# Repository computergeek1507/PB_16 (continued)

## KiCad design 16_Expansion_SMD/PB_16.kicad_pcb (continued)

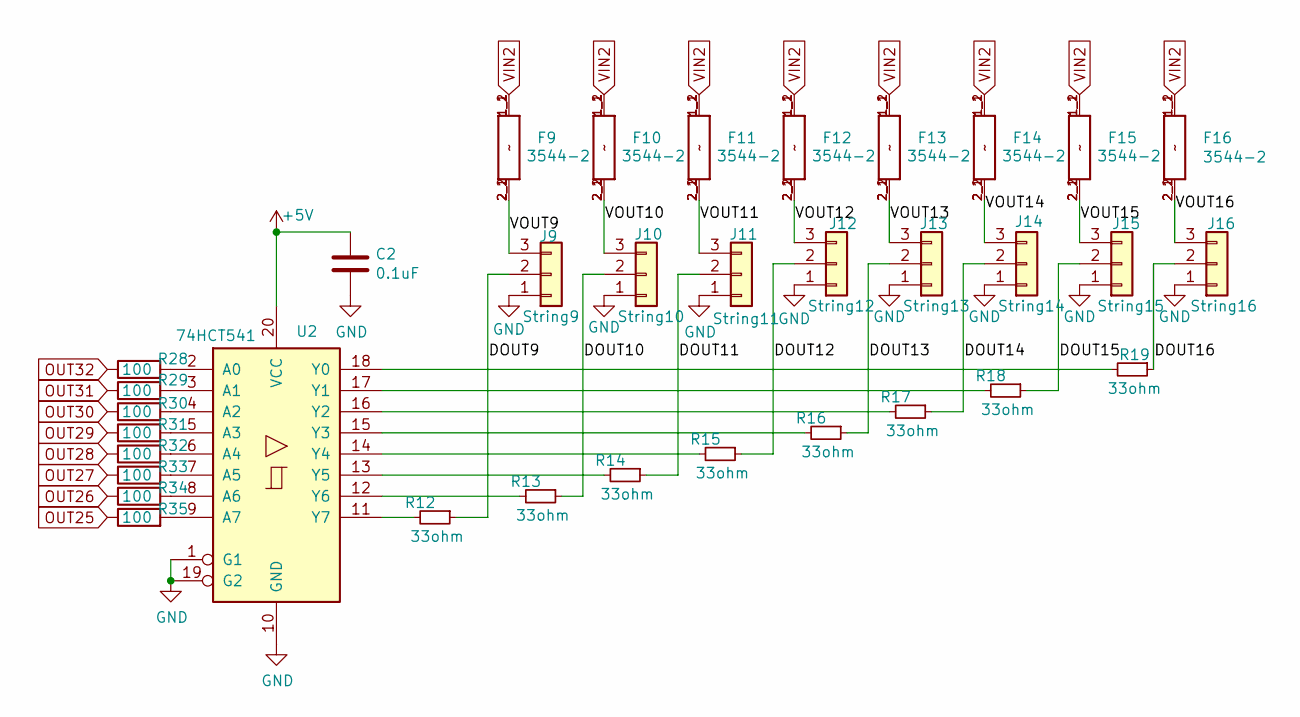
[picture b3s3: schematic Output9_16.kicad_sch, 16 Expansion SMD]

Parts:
C2: 0.1uF; C_0402_1005Metric; MPN 08055C104KAT2A; Digi-Key_PN 478-1395-1-ND
F9, F10, F11, F12, F13, F14, F15, F16: 3544-2; FUSE_3544-2; MPN 3544-2; Digi-Key_PN 36-3544-2-ND
J9: String9; PhoenixContact_MCV_3.81mm_3.5mm_1x03_Vertical; MPN 1843619/OSTTJ0311530; Digi-Key_PN 277-5737-ND/ED10555-ND
J10: String10; PhoenixContact_MCV_3.81mm_3.5mm_1x03_Vertical; MPN 1843619/OSTTJ0311530; Digi-Key_PN 277-5737-ND/ED10555-ND
J11: String11; PhoenixContact_MCV_3.81mm_3.5mm_1x03_Vertical; MPN 1843619/OSTTJ0311530; Digi-Key_PN 277-5737-ND/ED10555-ND
J12: String12; PhoenixContact_MCV_3.81mm_3.5mm_1x03_Vertical; MPN 1843619/OSTTJ0311530; Digi-Key_PN 277-5737-ND/ED10555-ND
J13: String13; PhoenixContact_MCV_3.81mm_3.5mm_1x03_Vertical; MPN 1843619/OSTTJ0311530; Digi-Key_PN 277-5737-ND/ED10555-ND
J14: String14; PhoenixContact_MCV_3.81mm_3.5mm_1x03_Vertical; MPN 1843619/OSTTJ0311530; Digi-Key_PN 277-5737-ND/ED10555-ND
J15: String15; PhoenixContact_MCV_3.81mm_3.5mm_1x03_Vertical; MPN 1843619/OSTTJ0311530; Digi-Key_PN 277-5737-ND/ED10555-ND
J16: String16; PhoenixContact_MCV_3.81mm_3.5mm_1x03_Vertical; MPN 1843619/OSTTJ0311530; Digi-Key_PN 277-5737-ND/ED10555-ND
R12, R13, R14, R15, R16, R17, R18, R19: 33ohm; R_0603_1608Metric; MPN RC0603JR-0733RL; LCSC_PN C23140
R28, R29, R30, R31, R32, R33, R34, R35: 100; R_0603_1608Metric
U2: 74HCT541; TSSOP-20_4.4x6.5mm_P0.65mm; LCSC C131314

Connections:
+5V: C2.1, U2.20 (VCC); also elsewhere on the board
/Output 9-16/DOUT9: J9.2, R12.1
/Output 9-16/DOUT10: J10.2, R13.1
/Output 9-16/DOUT11: J11.2, R14.1
/Output 9-16/DOUT12: J12.2, R15.1
/Output 9-16/DOUT13: J13.2, R16.1
/Output 9-16/DOUT14: J14.2, R17.1
/Output 9-16/DOUT15: J15.2, R18.1
/Output 9-16/DOUT16: J16.2, R19.1
/Output 9-16/VOUT9: F9.2_1 (2), F9.2_2 (2), J9.3
/Output 9-16/VOUT10: F10.2_1 (2), F10.2_2 (2), J10.3
/Output 9-16/VOUT11: F11.2_1 (2), F11.2_2 (2), J11.3
/Output 9-16/VOUT12: F12.2_1 (2), F12.2_2 (2), J12.3
/Output 9-16/VOUT13: F13.2_1 (2), F13.2_2 (2), J13.3
/Output 9-16/VOUT14: F14.2_1 (2), F14.2_2 (2), J14.3
/Output 9-16/VOUT15: F15.2_1 (2), F15.2_2 (2), J15.3
/Output 9-16/VOUT16: F16.2_1 (2), F16.2_2 (2), J16.3
GND: C2.2, J9.1, J10.1, J11.1, J12.1, J13.1, J14.1, J15.1, J16.1, U2.1 (G1), U2.10 (GND), U2.19 (G2); also elsewhere on the board
unnamed: R28.2, U2.2 (A0)
unnamed: R29.2, U2.3 (A1)
unnamed: R30.2, U2.4 (A2)
unnamed: R31.2, U2.5 (A3)
unnamed: R32.2, U2.6 (A4)
unnamed: R33.2, U2.7 (A5)
unnamed: R34.2, U2.8 (A6)
unnamed: R35.2, U2.9 (A7)
unnamed: R19.2, U2.18 (Y0)
unnamed: R18.2, U2.17 (Y1)
unnamed: R17.2, U2.16 (Y2)
unnamed: R16.2, U2.15 (Y3)
unnamed: R15.2, U2.14 (Y4)
unnamed: R14.2, U2.13 (Y5)
unnamed: R13.2, U2.12 (Y6)
unnamed: R12.2, U2.11 (Y7)
OUT25: R35.1; also elsewhere on the board
OUT26: R34.1; also elsewhere on the board
OUT27: R33.1; also elsewhere on the board
OUT28: R32.1; also elsewhere on the board
OUT29: R31.1; also elsewhere on the board
OUT30: R30.1; also elsewhere on the board
OUT31: R29.1; also elsewhere on the board
OUT32: R28.1; also elsewhere on the board
VIN2: F9.1_1 (1), F9.1_2 (1), F10.1_1 (1), F10.1_2 (1), F11.1_1 (1), F11.1_2 (1), F12.1_1 (1), F12.1_2 (1), F13.1_1 (1), F13.1_2 (1), F14.1_1 (1), F14.1_2 (1), F15.1_1 (1), F15.1_2 (1), F16.1_1 (1), F16.1_2 (1); also elsewhere on the board

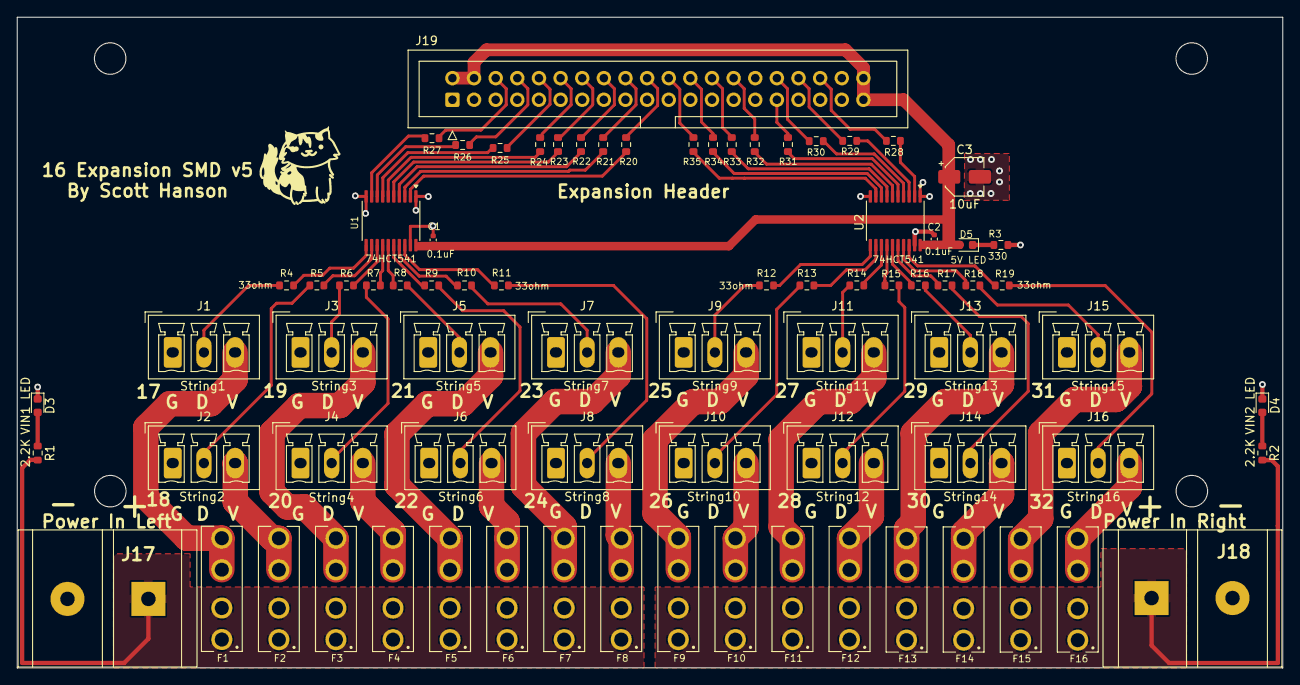
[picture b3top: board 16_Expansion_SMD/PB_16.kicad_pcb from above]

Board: 2 copper layers, 148.6 x 76.4 mm, 82 parts (0 on the bottom side), 87 nets.

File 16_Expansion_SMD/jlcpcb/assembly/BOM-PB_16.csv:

Comment,Designator,Footprint,LCSC
1K,"R1,R2",R_0805_2012Metric_Pad1.15x1.40mm_HandSolder,C17513
330,R3,R_0805_2012Metric_Pad1.15x1.40mm_HandSolder,C17630
VIN1 LED,"D3,D4,D5",LED_0805_2012Metric_Pad1.15x1.40mm_HandSolder,C2297
100,"R20,R21,R22,R23,R24,R25,R26,R27,R28,R29,R30,R31,R32,R33,R34,R35",R_0603_1608Metric_Pad0.98x0.95mm_HandSolder,C25804
0.1uF,"C1,C2",C_0805_2012Metric_Pad1.15x1.40mm_HandSolder,C49678
74HC245,"U1,U2",SOIC-20W_7.5x12.8mm_P1.27mm,C5625
10uF,C3,CP_Elec_4x5.3,C72485
String2,J2,"PhoenixContact_MCV_1,5_3-G-3.5_1x03_P3.50mm_Vertical",
String5,J5,"PhoenixContact_MCV_1,5_3-G-3.5_1x03_P3.50mm_Vertical",
String6,J6,"PhoenixContact_MCV_1,5_3-G-3.5_1x03_P3.50mm_Vertical",
String7,J7,"PhoenixContact_MCV_1,5_3-G-3.5_1x03_P3.50mm_Vertical",
String8,J8,"PhoenixContact_MCV_1,5_3-G-3.5_1x03_P3.50mm_Vertical",
String9,J9,"PhoenixContact_MCV_1,5_3-G-3.5_1x03_P3.50mm_Vertical",
String10,J10,"PhoenixContact_MCV_1,5_3-G-3.5_1x03_P3.50mm_Vertical",
String11,J11,"PhoenixContact_MCV_1,5_3-G-3.5_1x03_P3.50mm_Vertical",
String12,J12,"PhoenixContact_MCV_1,5_3-G-3.5_1x03_P3.50mm_Vertical",
String13,J13,"PhoenixContact_MCV_1,5_3-G-3.5_1x03_P3.50mm_Vertical",
String14,J14,"PhoenixContact_MCV_1,5_3-G-3.5_1x03_P3.50mm_Vertical",
String15,J15,"PhoenixContact_MCV_1,5_3-G-3.5_1x03_P3.50mm_Vertical",
String16,J16,"PhoenixContact_MCV_1,5_3-G-3.5_1x03_P3.50mm_Vertical",
3544-2,F1,FUSE_3544-2,
3544-2,F7,FUSE_3544-2,
3544-2,F14,FUSE_3544-2,
3544-2,F2,FUSE_3544-2,
3544-2,F6,FUSE_3544-2,
3544-2,F8,FUSE_3544-2,
3544-2,F9,FUSE_3544-2,
3544-2,F10,FUSE_3544-2,
3544-2,F16,FUSE_3544-2,
3544-2,F5,FUSE_3544-2,
3544-2,F3,FUSE_3544-2,
3544-2,F13,FUSE_3544-2,
33,RN1,R_Array_SIP8,
3544-2,F11,FUSE_3544-2,
33,RN3,R_Array_SIP8,
33,RN4,R_Array_SIP8,
33,RN2,R_Array_SIP8,
3544-2,F4,FUSE_3544-2,
String1,J1,"PhoenixContact_MCV_1,5_3-G-3.5_1x03_P3.50mm_Vertical",
String3,J3,"PhoenixContact_MCV_1,5_3-G-3.5_1x03_P3.50mm_Vertical",
String4,J4,"PhoenixContact_MCV_1,5_3-G-3.5_1x03_P3.50mm_Vertical",
3544-2,F15,FUSE_3544-2,
3544-2,F12,FUSE_3544-2,
Expansion Header,J19,IDC-Header_2x20_P2.54mm_Vertical,
Power In Left,J17,BARRIER_BLOCK_1ROW_2POS_P9.5MM,
Power In Right,J18,BARRIER_BLOCK_1ROW_2POS_P9.5MM,

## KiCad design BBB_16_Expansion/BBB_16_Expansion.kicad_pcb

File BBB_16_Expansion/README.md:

# Copyright and Disclaimer
Copyright: Scott Hanson

This documentation describes Open Hardware and is licensed under the CERN Open Hardware License Version 2 - Strongly Reciprocal. (CERN-OHL-S)

You may redistribute and modify this documentation under the terms of the CERN OHL-S-v2 (https://ohwr.org/cern_ohl_s_v2.txt). This documentation is distributed WITHOUT ANY EXPRESS OR IMPLIED WARRANTY, INCLUDING OF MERCHANTABILITY, SATISFACTORY QUALITY AND FITNESS FOR A PARTICULAR PURPOSE. Please see the CERN OHL v2-S for applicable conditions

**Under CERN OHL-S-v2, derivative work must be publicly released as defined in subsection 3.3**

# BBB 16 Expansion

**This board is untested, use at your own risk**

The BBB16 Expansion is a version of the BBB16 for the Falcon v4 Expansion Boards. It can be used with three expansion boards, 48 outputs. The design is surface mount. All the design files are open source and available on github.

To order PCBs upload the "GERBER-BBB_16_Expansion.zip" file in the "jlcpcb\gerber" folder to jlcpcb.com. Enable the SMD service, 'BOM-BBB_16_Expansion.csv' is the SMD BOM and 'POS-BBB_16_Expansion.csv' is the SMD CPL position file.

## [Part BOM](https://github.com/computergeek1507/PB_16/raw/master/BBB_16_Expansion/BBB_16_Expansion_BOM.ods)

## [Interactive BOM](https://computergeek1507.github.io/PB_16/BBB_16_Expansion/bom/ibom)

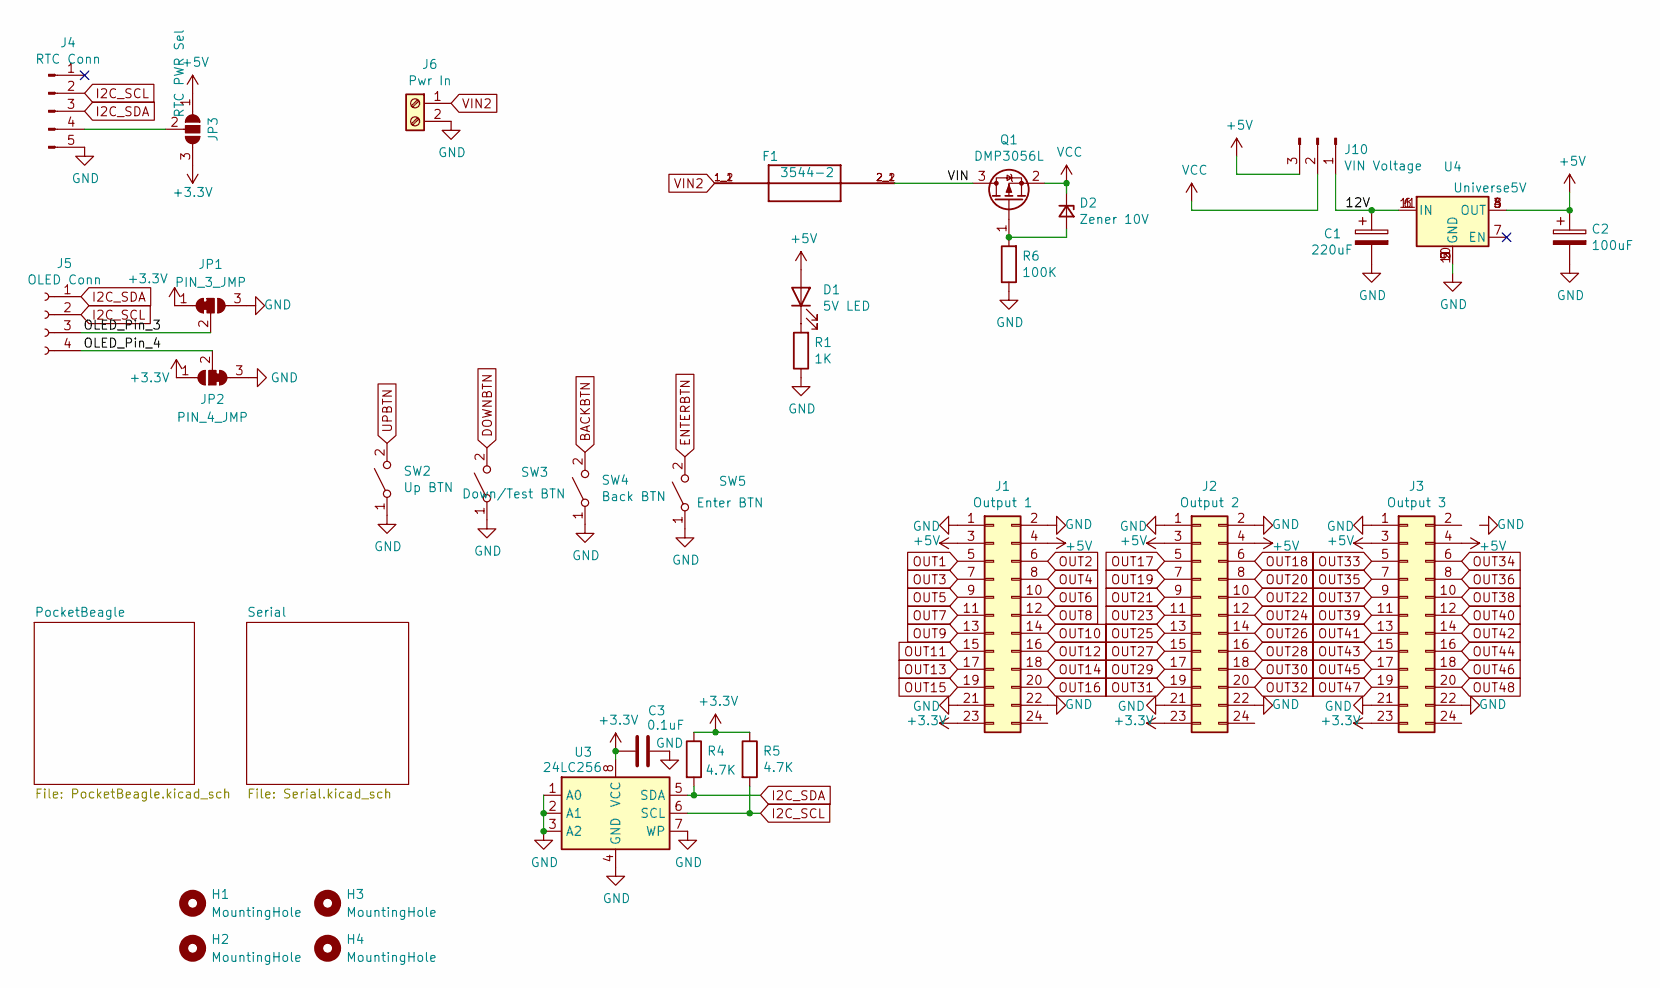
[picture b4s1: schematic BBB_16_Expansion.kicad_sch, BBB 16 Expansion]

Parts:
C1: 220uF; CP_Radial_D10.0mm_P5.00mm; MPN ECA-1HM221; Digi-Key_PN P5183-ND
C2: 100uF; CP_Elec_6.3x5.4_Nichicon; MPN UWX1C101MCL1GB; Digi-Key_PN 493-2105-1-ND
C3: 0.1uF; C_0603_1608Metric_Pad1.08x0.95mm_HandSolder; MPN CC0603KRX7R9BB104; Digi-Key_PN 1276-1007-1-ND
D1: 5V LED; LED_0603_1608Metric_Pad1.05x0.95mm_HandSolder; MPN LTST-C171GKT; Digi-Key_PN 160-1423-1-ND
D2: Zener 10V; D_SOD-123; MPN MMSZ5240B-7-F; Digi-Key_PN MMSZ5240B-FDICT-ND
F1: 3544-2; FUSE_3544-2; MPN 3544-2; Digi-Key_PN 36-3544-2-ND
H1, H2, H3, H4: MountingHole; MountingHole_3.5mm
J1: Output 1; OST_302-S241; MPN Z-S311024S1GK1A; Digi-Key_PN ED10525-ND
J2: Output 2; OST_302-S241; MPN Z-S311024S1GK1A; Digi-Key_PN ED10525-ND
J3: Output 3; OST_302-S241; MPN Z-S311024S1GK1A; Digi-Key_PN ED10525-ND
J4: RTC Conn; PinHeader_1x05_P2.54mm_Vertical; MPN MTP125-1105S1; Digi-Key_PN 732-5318-ND
J5: OLED Conn; OLED-SSD1306-128X64-I2C-THT; MPN A2541HWV-4P; Digi-Key_PN S7002-ND
J6: Pwr In; PHOENIX_MKDS1_2-3.81; MPN 1727010; Digi-Key_PN 277-1947-ND
J10: VIN Voltage; PinHeader_1x03_P2.54mm_Vertical; MPN 61300311121; Digi-Key_PN 732-5316-ND
JP1: PIN_3_JMP; SolderJumper-3_P1mm_Bridged12
JP2: PIN_4_JMP; SolderJumper-3_P1mm_Bridged23
JP3: RTC PWR Sel; SolderJumper-3_P1.3mm_Open_Pad1.0x1.5mm
Q1: DMP3056L; SOT-23; MPN DMP3056L-7; Digi-Key_PN DMP3056L-7DICT-ND
R1: 1K; R_0603_1608Metric_Pad0.98x0.95mm_HandSolder; MPN RC0805FR-071KL; Digi-Key_PN 311-1.00KCRCT-ND
R4, R5: 4.7K; R_0603_1608Metric_Pad0.98x0.95mm_HandSolder; MPN RC0805JR-074K7L; Digi-Key_PN 311-4.7KARCT-ND
R6: 100K; R_0603_1608Metric_Pad0.98x0.95mm_HandSolder; MPN RT0603BRD07100KL; Digi-Key_PN YAG1235CT-ND
SW2: Up BTN; SW_PUSH_6mm; MPN 1825910-6; Digi-Key_PN 450-1650-ND
SW3: Down/Test BTN; SW_PUSH_6mm; MPN 1825910-6; Digi-Key_PN 450-1650-ND
SW4: Back BTN; SW_PUSH_6mm; MPN 1825910-6; Digi-Key_PN 450-1650-ND
SW5: Enter BTN; SW_PUSH_6mm; MPN 1825910-6; Digi-Key_PN 450-1650-ND
U3: 24LC256; SOIC-8_3.9x4.9mm_P1.27mm; MPN 24LC256T-I/SN; Digi-Key_PN 24LC256T-I/SNCT-ND
U4: Universe5V; Universal_5V_Horizontal; MPN OKI-78SR-5/1.5-W36-C; Digi-Key_PN 811-2196-5-ND

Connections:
+3V3: C3.2, J1.23, J2.23, J3.23, JP1.1 (A), JP2.1 (A), JP3.3 (B), R4.1, R5.1, U3.8 (VCC); also elsewhere on the board
+5V: C2.1, D1.2 (A), J1.3, J1.4, J2.3, J2.4, J3.3, J3.4, J10.3, JP3.1 (A), U4.3 (OUT), U4.4 (OUT), U4.8 (OUT); also elsewhere on the board
/12V: C1.1, J10.1, U4.1 (IN), U4.6 (IN), U4.11 (IN)
/OLED_Pin_3: J5.3, JP1.2 (C)
/OLED_Pin_4: J5.4, JP2.2 (C)
/VIN: F1.2_1 (2), F1.2_2 (2), Q1.3 (D)
BACKBTN: SW4.2 (B); also elsewhere on the board
DOWNBTN: SW3.2 (B); also elsewhere on the board
ENTERBTN: SW5.2 (B); also elsewhere on the board
GND: C1.2, C2.2, C3.1, J1.1, J1.2, J1.21, J1.22, J2.1, J2.2, J2.21, J2.22, J3.1, J3.21, J3.22, J4.5, J6.2, JP1.3 (B), JP2.3 (B), R1.1, R6.1, SW2.1 (A), SW3.1 (A), SW4.1 (A), SW5.1 (A), U3.1 (A0), U3.2 (A1), U3.3 (A2), U3.4 (GND), U3.7 (WP), U4.2 (GND), U4.5 (GND), U4.9 (GND), U4.10 (GND); also elsewhere on the board
I2C_SCL: J4.2, J5.2, R5.2, U3.6 (SCL); also elsewhere on the board
I2C_SDA: J4.3, J5.1, R4.2, U3.5 (SDA); also elsewhere on the board
unnamed: D1.1 (K), R1.2
unnamed: D2.2 (A), Q1.1 (G), R6.2
unnamed: J4.4, JP3.2 (C)
OUT1: J1.5; also elsewhere on the board
OUT2: J1.6; also elsewhere on the board
OUT3: J1.7; also elsewhere on the board
OUT4: J1.8; also elsewhere on the board
OUT5: J1.9; also elsewhere on the board
OUT6: J1.10; also elsewhere on the board
OUT7: J1.11; also elsewhere on the board
OUT8: J1.12; also elsewhere on the board
OUT9: J1.13; also elsewhere on the board
OUT10: J1.14; also elsewhere on the board
OUT11: J1.15; also elsewhere on the board
OUT12: J1.16; also elsewhere on the board
OUT13: J1.17; also elsewhere on the board
OUT14: J1.18; also elsewhere on the board
OUT15: J1.19; also elsewhere on the board
OUT16: J1.20; also elsewhere on the board
OUT17: J2.5; also elsewhere on the board
OUT18: J2.6; also elsewhere on the board
OUT19: J2.7; also elsewhere on the board
OUT20: J2.8; also elsewhere on the board
OUT21: J2.9; also elsewhere on the board
OUT22: J2.10; also elsewhere on the board
OUT23: J2.11; also elsewhere on the board
OUT24: J2.12; also elsewhere on the board
OUT25: J2.13; also elsewhere on the board
OUT26: J2.14; also elsewhere on the board
OUT27: J2.15; also elsewhere on the board
OUT28: J2.16; also elsewhere on the board
OUT29: J2.17; also elsewhere on the board
OUT30: J2.18; also elsewhere on the board
OUT31: J2.19; also elsewhere on the board
OUT32: J2.20; also elsewhere on the board
OUT33: J3.5; also elsewhere on the board
OUT34: J3.6; also elsewhere on the board
OUT35: J3.7; also elsewhere on the board
OUT36: J3.8; also elsewhere on the board
OUT37: J3.9; also elsewhere on the board
OUT38: J3.10; also elsewhere on the board
OUT39: J3.11; also elsewhere on the board
OUT40: J3.12; also elsewhere on the board
OUT41: J3.13; also elsewhere on the board
OUT42: J3.14; also elsewhere on the board
OUT43: J3.15; also elsewhere on the board
OUT44: J3.16; also elsewhere on the board
OUT45: J3.17; also elsewhere on the board
OUT46: J3.18; also elsewhere on the board
OUT47: J3.19; also elsewhere on the board
OUT48: J3.20; also elsewhere on the board
UPBTN: SW2.2 (B); also elsewhere on the board
VCC: D2.1 (K), J10.2, Q1.2 (S)
VIN2: F1.1_1 (1), F1.1_2 (1), J6.1

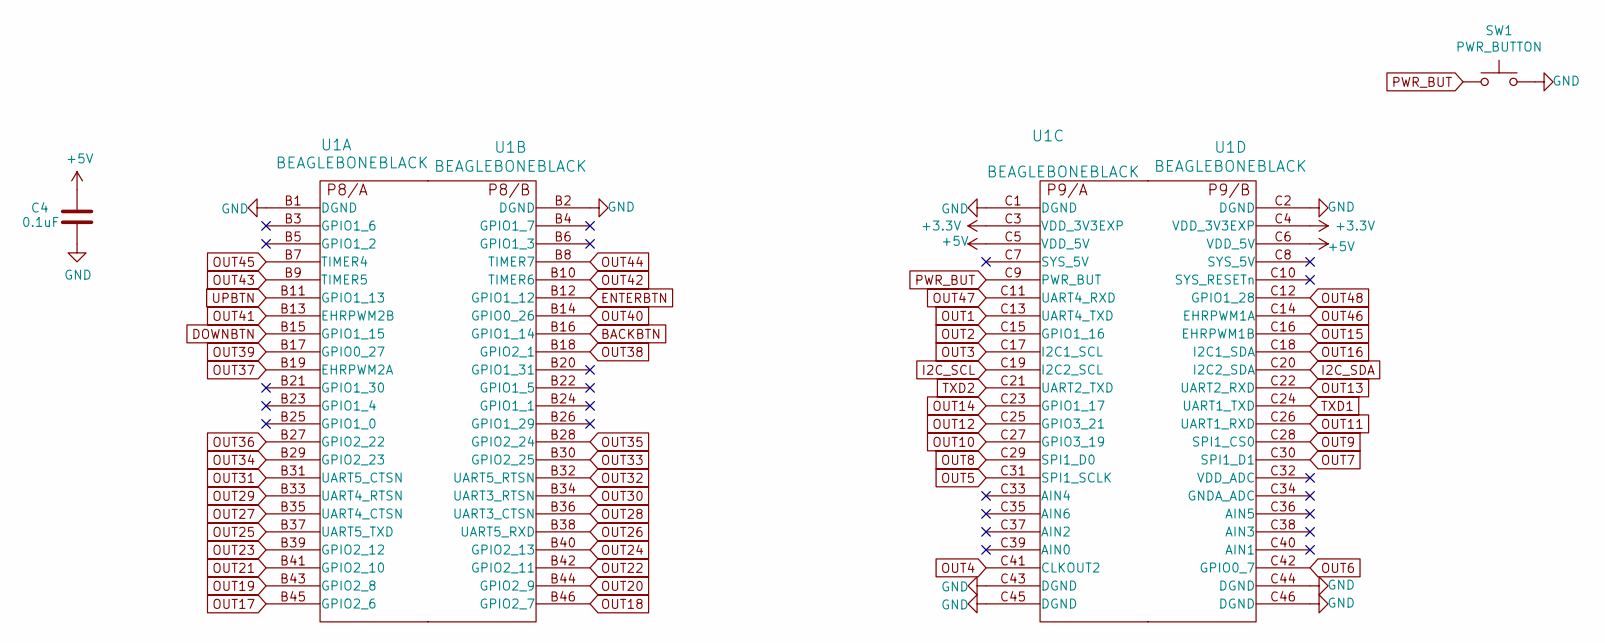
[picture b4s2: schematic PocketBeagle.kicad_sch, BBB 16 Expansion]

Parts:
C4: 0.1uF; C_0603_1608Metric_Pad1.08x0.95mm_HandSolder; MPN CC0603KRX7R9BB104; Digi-Key_PN 1276-1007-1-ND
SW1: PWR_BUTTON; SW_PUSH_6mm; MPN 1825910-6; Digi-Key_PN 450-1650-ND
U1: BEAGLEBONEBLACK

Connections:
+3V3: U1.C3 (VDD_3V3EXP), U1.C4 (VDD_3V3EXP); also elsewhere on the board
+5V: C4.1, U1.C5 (VDD_5V), U1.C6 (VDD_5V); also elsewhere on the board
BACKBTN: U1.B16 (GPIO1_14); also elsewhere on the board
DOWNBTN: U1.B15 (GPIO1_15); also elsewhere on the board
ENTERBTN: U1.B12 (GPIO1_12); also elsewhere on the board
GND: C4.2, SW1.2, U1.B1 (DGND), U1.B2 (DGND), U1.C1 (DGND), U1.C2 (DGND), U1.C43 (DGND), U1.C44 (DGND), U1.C45 (DGND), U1.C46 (DGND); also elsewhere on the board
I2C_SCL: U1.C19 (I2C2_SCL); also elsewhere on the board
I2C_SDA: U1.C20 (I2C2_SDA); also elsewhere on the board
OUT1: U1.C13 (UART4_TXD); also elsewhere on the board
OUT2: U1.C15 (GPIO1_16); also elsewhere on the board
OUT3: U1.C17 (I2C1_SCL); also elsewhere on the board
OUT4: U1.C41 (CLKOUT2); also elsewhere on the board
OUT5: U1.C31 (SPI1_SCLK); also elsewhere on the board
OUT6: U1.C42 (GPIO0_7); also elsewhere on the board
OUT7: U1.C30 (SPI1_D1); also elsewhere on the board
OUT8: U1.C29 (SPI1_D0); also elsewhere on the board
OUT9: U1.C28 (SPI1_CS0); also elsewhere on the board
OUT10: U1.C27 (GPIO3_19); also elsewhere on the board
OUT11: U1.C26 (UART1_RXD); also elsewhere on the board
OUT12: U1.C25 (GPIO3_21); also elsewhere on the board
OUT13: U1.C22 (UART2_RXD); also elsewhere on the board
OUT14: U1.C23 (GPIO1_17); also elsewhere on the board
OUT15: U1.C16 (EHRPWM1B); also elsewhere on the board
OUT16: U1.C18 (I2C1_SDA); also elsewhere on the board
OUT17: U1.B45 (GPIO2_6); also elsewhere on the board
OUT18: U1.B46 (GPIO2_7); also elsewhere on the board
OUT19: U1.B43 (GPIO2_8); also elsewhere on the board
OUT20: U1.B44 (GPIO2_9); also elsewhere on the board
OUT21: U1.B41 (GPIO2_10); also elsewhere on the board
OUT22: U1.B42 (GPIO2_11); also elsewhere on the board
OUT23: U1.B39 (GPIO2_12); also elsewhere on the board
OUT24: U1.B40 (GPIO2_13); also elsewhere on the board
OUT25: U1.B37 (UART5_TXD); also elsewhere on the board
OUT26: U1.B38 (UART5_RXD); also elsewhere on the board
OUT27: U1.B35 (UART4_CTSN); also elsewhere on the board
OUT28: U1.B36 (UART3_CTSN); also elsewhere on the board
OUT29: U1.B33 (UART4_RTSN); also elsewhere on the board
OUT30: U1.B34 (UART3_RTSN); also elsewhere on the board
OUT31: U1.B31 (UART5_CTSN); also elsewhere on the board
OUT32: U1.B32 (UART5_RTSN); also elsewhere on the board
OUT33: U1.B30 (GPIO2_25); also elsewhere on the board
OUT34: U1.B29 (GPIO2_23); also elsewhere on the board
OUT35: U1.B28 (GPIO2_24); also elsewhere on the board
OUT36: U1.B27 (GPIO2_22); also elsewhere on the board
OUT37: U1.B19 (EHRPWM2A); also elsewhere on the board
OUT38: U1.B18 (GPIO2_1); also elsewhere on the board
OUT39: U1.B17 (GPIO0_27); also elsewhere on the board
OUT40: U1.B14 (GPIO0_26); also elsewhere on the board
OUT41: U1.B13 (EHRPWM2B); also elsewhere on the board
OUT42: U1.B10 (TIMER6); also elsewhere on the board
OUT43: U1.B9 (TIMER5); also elsewhere on the board
OUT44: U1.B8 (TIMER7); also elsewhere on the board
OUT45: U1.B7 (TIMER4); also elsewhere on the board
OUT46: U1.C14 (EHRPWM1A); also elsewhere on the board
OUT47: U1.C11 (UART4_RXD); also elsewhere on the board
OUT48: U1.C12 (GPIO1_28); also elsewhere on the board
PWR_BUT: SW1.1, U1.C9 (PWR_BUT)
TXD1: U1.C24 (UART1_TXD); also elsewhere on the board
TXD2: U1.C21 (UART2_TXD); also elsewhere on the board
UPBTN: U1.B11 (GPIO1_13); also elsewhere on the board

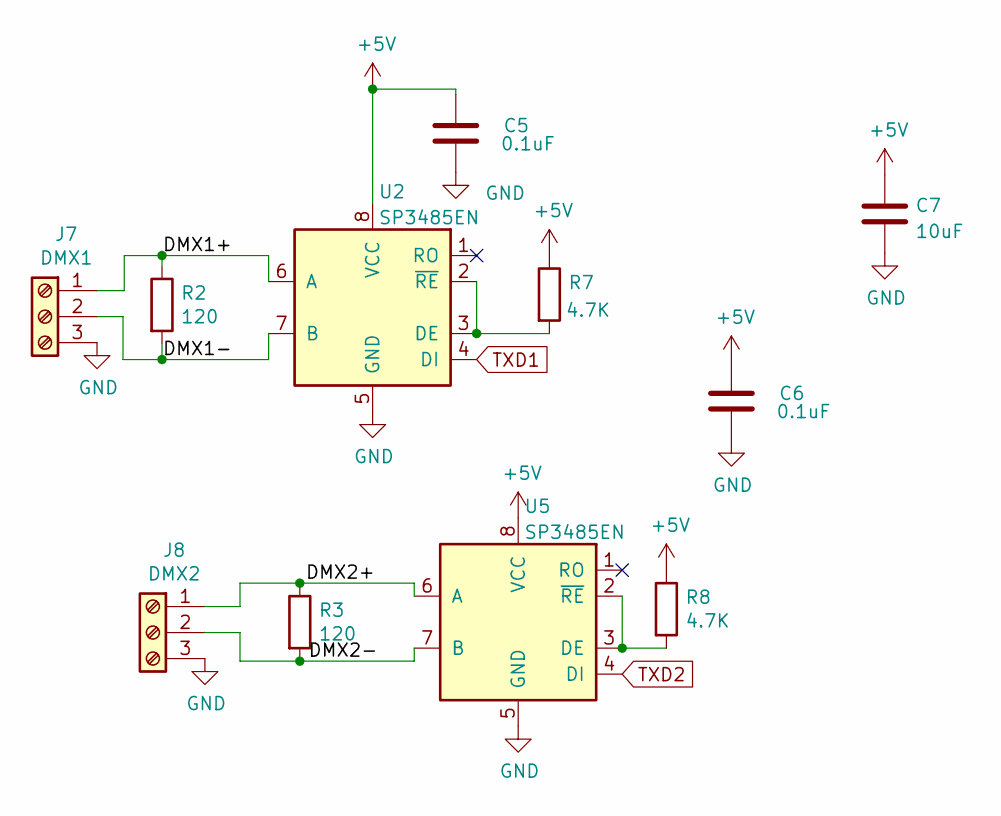
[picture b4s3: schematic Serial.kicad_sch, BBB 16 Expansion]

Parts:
C5, C6: 0.1uF; C_0603_1608Metric_Pad1.08x0.95mm_HandSolder; MPN CC0603KRX7R9BB104; Digi-Key_PN 1276-1007-1-ND
C7: 10uF; CP_Elec_4x5.3; MPN UWT1C100MCL1GB; Digi-Key_PN 493-2173-1-ND
J7: DMX1; PhoenixContact_MCV_1,5_3-G-3.81_1x03_P3.81mm_Vertical; MPN EBWA-03-B; Digi-Key_PN 2057-EBWA-03-B-ND
J8: DMX2; PhoenixContact_MCV_1,5_3-G-3.81_1x03_P3.81mm_Vertical; MPN EBWA-03-B; Digi-Key_PN 2057-EBWA-03-B-ND
R2, R3: 120; R_0603_1608Metric_Pad0.98x0.95mm_HandSolder; MPN RC0805JR-07120RL; Digi-Key_PN 311-120ARCT-ND
R7, R8: 4.7K; R_0603_1608Metric_Pad0.98x0.95mm_HandSolder; MPN RC0805JR-074K7L; Digi-Key_PN 311-4.7KARCT-ND
U2, U5: SP3485EN; SOIC-8_3.9x4.9mm_P1.27mm; MPN SP485EEN-L; Digi-Key_PN 1016-1171-5-ND

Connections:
+5V: C5.1, C6.1, C7.1, R7.1, R8.1, U2.8 (VCC), U5.8 (VCC); also elsewhere on the board
/Serial/DMX1+: J7.1, R2.1, U2.6 (A)
/Serial/DMX1-: J7.2, R2.2, U2.7 (B)
/Serial/DMX2+: J8.1, R3.1, U5.6 (A)
/Serial/DMX2-: J8.2, R3.2, U5.7 (B)
GND: C5.2, C6.2, C7.2, J7.3, J8.3, U2.5 (GND), U5.5 (GND); also elsewhere on the board
unnamed: R7.2, U2.2 (~RE), U2.3 (DE)
unnamed: R8.2, U5.2 (~RE), U5.3 (DE)
TXD1: U2.4 (DI); also elsewhere on the board
TXD2: U5.4 (DI); also elsewhere on the board

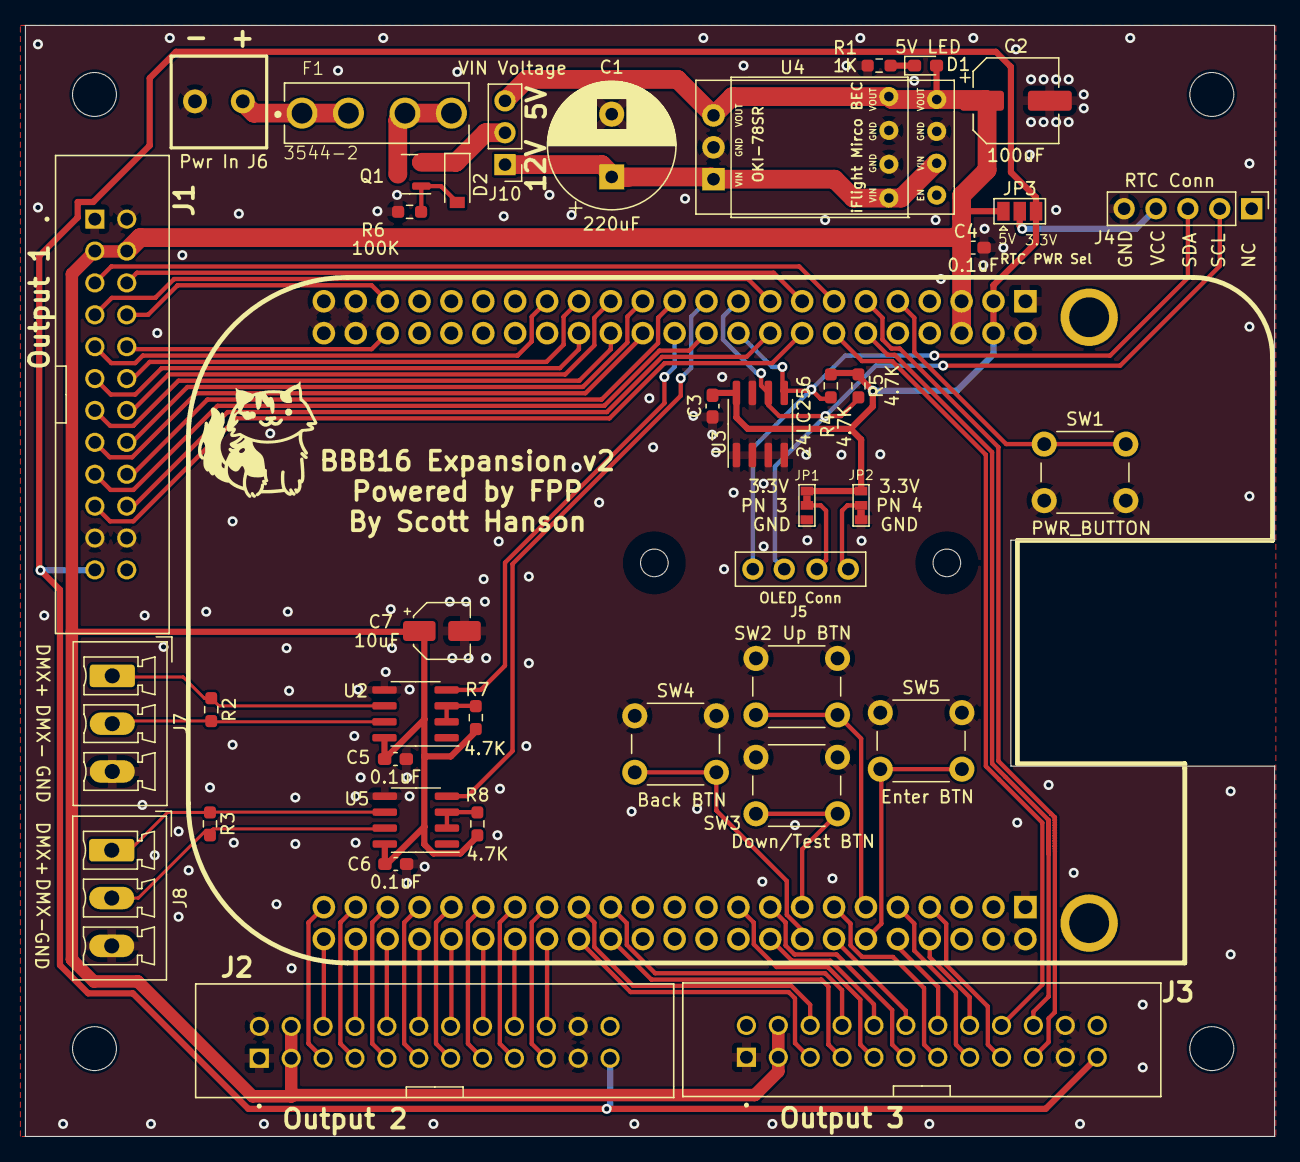
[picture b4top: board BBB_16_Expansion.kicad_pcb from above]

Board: 2 copper layers, 99.5 x 88.5 mm, 45 parts (0 on the bottom side), 75 nets.

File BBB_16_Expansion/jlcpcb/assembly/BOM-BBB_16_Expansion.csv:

Comment,Designator,Footprint,LCSC
100uF,C2,CP_Elec_6.3x5.4_Nichicon,C134723
0.1uF,"C3,C4,C5,C6",C_0603_1608Metric_Pad1.08x0.95mm_HandSolder,C14663
DMP3056L,Q1,SOT-23,C150724
Zener 10V,D2,D_SOD-123,C173431
120,"R2,R3",R_0603_1608Metric_Pad0.98x0.95mm_HandSolder,C17437
1K,R1,R_0603_1608Metric_Pad0.98x0.95mm_HandSolder,C17513
4.7K,"R4,R5,R7,R8",R_0603_1608Metric_Pad0.98x0.95mm_HandSolder,C17673
Output 1,"J1,J2,J3",OST_302-S241,C221083
OLED Conn,J5,OLED-SSD1306-128X64-I2C-THT,C225501
5V LED,D1,LED_0603_1608Metric_Pad1.05x0.95mm_HandSolder,C2297
100K,R6,R_0603_1608Metric_Pad0.98x0.95mm_HandSolder,C25803
RTC Conn,J4,PinHeader_1x05_P2.54mm_Vertical,C358687
DMX1,"J7,J8",PhoenixContact_MCV_3.81mm_3.5mm_1x03_Vertical,C36780
PWR_BUTTON,"SW1,SW2,SW3,SW4,SW5",SW_PUSH_6mm,C428628
VIN Voltage,J10,PinHeader_1x03_P2.54mm_Vertical,C49257
3544-2,F1,FUSE_3544-2,C492610
24LC256,U3,SOIC-8_3.9x4.9mm_P1.27mm,C6482
SP3485EN,"U2,U5",SOIC-8_3.9x4.9mm_P1.27mm,C6855
Pwr In,J6,PHOENIX_MKDS1_2-3.81,C69811
10uF,C7,CP_Elec_4x5.3,C72485
220uF,C1,CP_Radial_D10.0mm_P5.00mm,C88784
Universe5V,U4,Universal_5V_Horizontal,
BEAGLEBONEBLACK,U1,BEAGLEBONEBLACK,

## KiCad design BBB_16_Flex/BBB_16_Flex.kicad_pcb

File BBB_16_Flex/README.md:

# Copyright and Disclaimer
Copyright: Scott Hanson

This documentation describes Open Hardware and is licensed under the CERN Open Hardware License Version 2 - Strongly Reciprocal. (CERN-OHL-S)

You may redistribute and modify this documentation under the terms of the CERN OHL-S-v2 (https://ohwr.org/cern_ohl_s_v2.txt). This documentation is distributed WITHOUT ANY EXPRESS OR IMPLIED WARRANTY, INCLUDING OF MERCHANTABILITY, SATISFACTORY QUALITY AND FITNESS FOR A PARTICULAR PURPOSE. Please see the CERN OHL v2-S for applicable conditions

**Under CERN OHL-S-v2, derivative work must be publicly released as defined in subsection 3.3**

# BBB 16 Flex

The BBB16 Flex is a version of the BBB16 for the HolidayCoro Flex System. It can be used with all three flex boards, 48 outputs. The design is surface mount. All the design files are open source and available on github.

## [Part BOM](https://github.com/computergeek1507/PB_16/raw/master/BBB_16_Flex/BBB_16_Flex_BOM.ods)

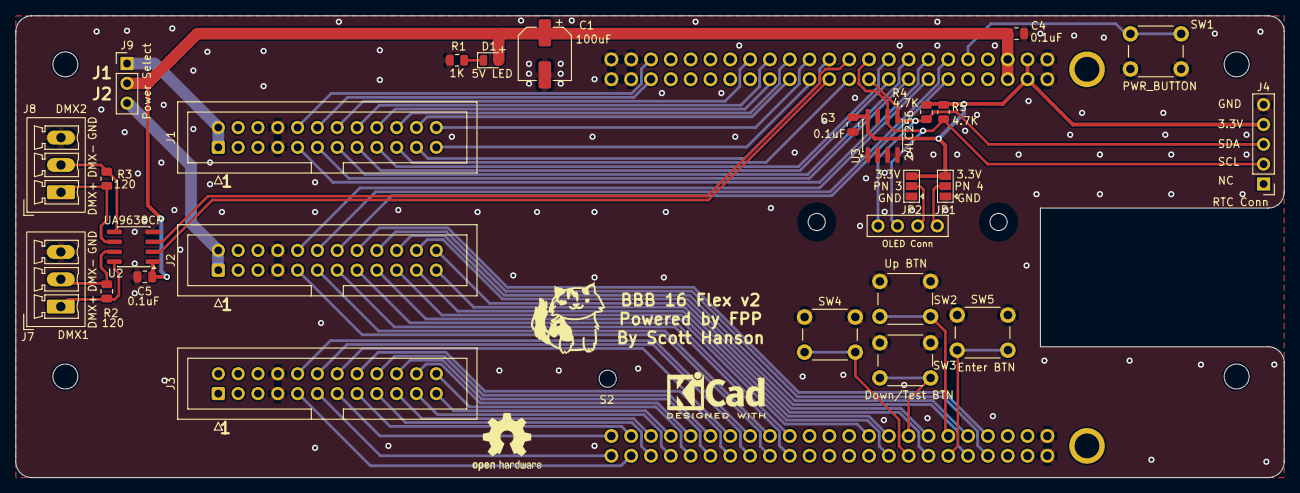
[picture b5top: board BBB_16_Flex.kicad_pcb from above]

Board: 2 copper layers, 162.6 x 59.2 mm, 29 parts (0 on the bottom side), 69 nets.

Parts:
C1: 100uF; CP_Elec_6.3x5.4_Nichicon
C3, C4, C5: 0.1uF; C_0805_2012Metric
D1: 5V LED; LED_0805_2012Metric
J1: Output 1; IDC-Header_2x12_P2.54mm_Vertical
J2: Output 2; IDC-Header_2x12_P2.54mm_Vertical
J3: Output 3; IDC-Header_2x12_P2.54mm_Vertical
J4: RTC Conn; PinHeader_1x05_P2.54mm_Vertical
J5: OLED Conn; OLED-SSD1306-128X64-I2C-THT
J7: DMX1; PhoenixContact_MCV_1,5_3-G-3.5_1x03_P3.50mm_Vertical
J8: DMX2; PhoenixContact_MCV_1,5_3-G-3.5_1x03_P3.50mm_Vertical
J9: Power Select; PinHeader_1x03_P2.54mm_Vertical
JP1, JP2: SolderJumper_3_Open; SolderJumper-3_P1.3mm_Open_Pad1.0x1.5mm
R1: 1K; R_0805_2012Metric
R2, R3: 120; R_0805_2012Metric
R4, R5: 4.7K; R_0805_2012Metric
S2: MountingHole_2.2mm_M2_ISO7380
SW1: PWR_BUTTON; SW_PUSH_6mm
SW2: Up BTN; SW_PUSH_6mm
SW3: Down/Test BTN; SW_PUSH_6mm
SW4: Back BTN; SW_PUSH_6mm
SW5: Enter BTN; SW_PUSH_6mm
U1: BEAGLEBONEBLACK
U2: UA9638CP; SOIC-8_3.9x4.9mm_P1.27mm
U3: 24LC256; SOIC-8_3.9x4.9mm_P1.27mm

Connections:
+3V3: C3.2, J4.4, JP1.3, JP2.3, R4.1, R5.1, U1.C3, U1.C4, U3.8
+5V: C1.1, C4.1, C5.1, D1.2, J9.2, U1.C5, U1.C6, U2.1
/OLED_Pin_3: J5.3, JP2.2
/OLED_Pin_4: J5.4, JP1.2
/PWR1: J1.1, J1.2, J9.1
/PWR2: J2.1, J2.2, J9.3
/Serial/DMX1+: J7.1, R2.1, U2.8
/Serial/DMX1-: J7.2, R2.2, U2.7
/Serial/DMX2+: J8.1, R3.1, U2.6
/Serial/DMX2-: J8.2, R3.2, U2.5
DOWNBTN: SW3.2, U1.B15
GND: C1.2, C3.1, C4.2, C5.2, J1.7, J1.8, J2.7, J2.8, J3.7, J3.8, J4.5, J7.3, J8.3, JP1.1, JP2.1, R1.1, SW1.2, SW2.1, SW3.1, SW4.1, SW5.1, U1.B1, U1.B2, U1.C1, U1.C2, U1.C43, U1.C44, U1.C45, U1.C46, U2.4, U3.1, U3.2, U3.3, U3.4, U3.7
I2C_SCL: J4.2, J5.2, R5.2, U1.C19, U3.6
I2C_SDA: J4.3, J5.1, R4.2, U1.C20, U3.5
LEFTBTN: SW4.2, U1.B16
unnamed: D1.1, R1.2
OUT1: J1.9, U1.C13
OUT2: J1.10, U1.C41
OUT3: J1.11, U1.C16
OUT4: J1.12, U1.C42
OUT5: J1.13, U1.C15
OUT6: J1.14, U1.C31
OUT7: J1.15, U1.C18
OUT8: J1.16, U1.C29
OUT9: J1.17, U1.C17
OUT10: J1.18, U1.C30
OUT11: J1.19, U1.C22
OUT12: J1.20, U1.C27
OUT13: J1.21, U1.C23
OUT14: J1.22, U1.C28
OUT15: J1.23, U1.C26
OUT16: J1.24, U1.C25
OUT17: J2.9, U1.B30
OUT18: J2.10, U1.C14
OUT19: J2.11, U1.B29
OUT20: J2.12, U1.C11
OUT21: J2.13, U1.B28
OUT22: J2.14, U1.C12
OUT23: J2.15, U1.B27
OUT24: J2.16, U1.B7
OUT25: J2.17, U1.B19
OUT26: J2.18, U1.B8
OUT27: J2.19, U1.B18
OUT28: J2.20, U1.B9
OUT29: J2.21, U1.B17
OUT30: J2.22, U1.B10
OUT31: J2.23, U1.B14
OUT32: J2.24, U1.B13
OUT33: J3.9, U1.B44
OUT34: J3.10, U1.B31
OUT35: J3.11, U1.B46
OUT36: J3.12, U1.B32
OUT37: J3.13, U1.B45
OUT38: J3.14, U1.B33
OUT39: J3.15, U1.B43
OUT40: J3.16, U1.B34
OUT41: J3.17, U1.B42
OUT42: J3.18, U1.B35
OUT43: J3.19, U1.B41
OUT44: J3.20, U1.B36
OUT45: J3.21, U1.B40
OUT46: J3.22, U1.B37
OUT47: J3.23, U1.B39
OUT48: J3.24, U1.B38
PWR_BUT: SW1.1, U1.C9
RIGHTBTN: SW5.2, U1.B12
TXD1: U1.C24, U2.2
TXD2: U1.C21, U2.3
UPBTN: SW2.2, U1.B11
